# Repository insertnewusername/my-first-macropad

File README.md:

# my-first-macropad

My-first-macropad is.... My first macropad.
Made this to experiment with hardware, as I thought this would be a nice first project for me. Still decide what the buttons should do, they'll probably like execute simple commands such as opening task manager, I'll figure it out once I get the hardware and update this.

<H1>HARDWARE!!!</H1>
Ok so this was my first time soldering and assembling a pcb, so I screwed up a lot, and it took me a while to figure everything out (still need practice), and after I finished doing everything, getting the firmware done was a nightmare, so asked AI how do i make QMK not gimme that many error messages and what's wrong, eventually got there. Case is still pending, but the overall thing is done, so I don't think a case is that strictly required

IMAGES!!!!

(BTW I messed up the pcb which is why the usb for xiao is faced that way oopsies)

<h1>CAD Model: </h1><br>
Made a basic frame for all the keys and usb. Hopefully everthing works out!

<h1>PCD:</h1>

Here's my PCB, I made this all in KiCad.

<h1>BOM</h1>

Here's what I need to create the hackpad:

6x Cherry MX Switches <br>
6x DSA Keycaps <br>
4x M3x5x4 Heatset inserts <br>
4x M3x12mm SHSC Bolts <br>
6x 1N4148 DO-35 Diodes <br>
1x XIAO RP2040 <br>
1x Case (2 3D printed parts to assemble case I hope I get a 3d printer sometime next year) <br>
1x Soldering Iron (I'm new to hardware - this is my first project)<br>
<br>
(Optional - I'll try add these later but pls give cuz i'll find a way to add em)<br>
2x WS2812B LEDs<br>
1x 0.91" 128x32 OLED Display<br>

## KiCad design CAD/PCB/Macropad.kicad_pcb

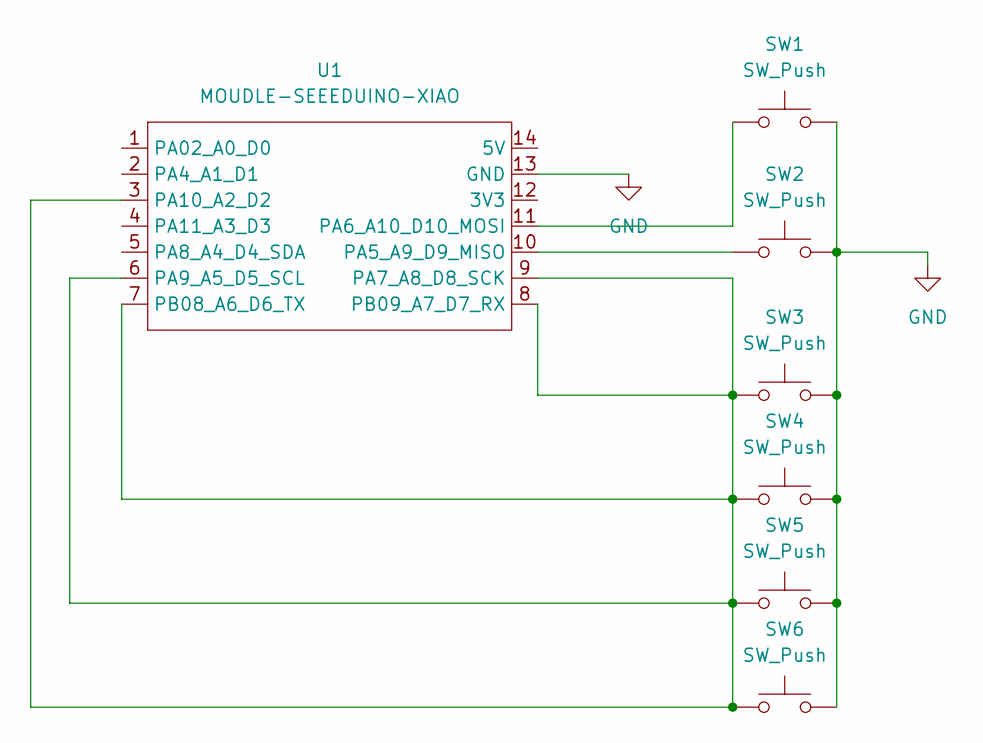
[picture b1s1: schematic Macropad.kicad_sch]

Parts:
SW1, SW2, SW3, SW4, SW5, SW6: SW_Push; SW_Cherry_MX_1.00u_PCB
U1: MOUDLE-SEEEDUINO-XIAO; XIAO-Generic-Hybrid-14P-2.54-21X17.8MM

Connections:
GND: SW1.2, SW2.2, SW3.2, SW4.2, SW5.2, SW6.2, U1.13 (GND)
unnamed: SW2.1, U1.10 (PA5_A9_D9_MISO)
unnamed: SW1.1, U1.11 (PA6_A10_D10_MOSI)
unnamed: SW3.1, SW4.1, SW5.1, SW6.1, U1.3 (PA10_A2_D2), U1.6 (PA9_A5_D5_SCL), U1.7 (PB08_A6_D6_TX), U1.8 (PB09_A7_D7_RX), U1.9 (PA7_A8_D8_SCK)

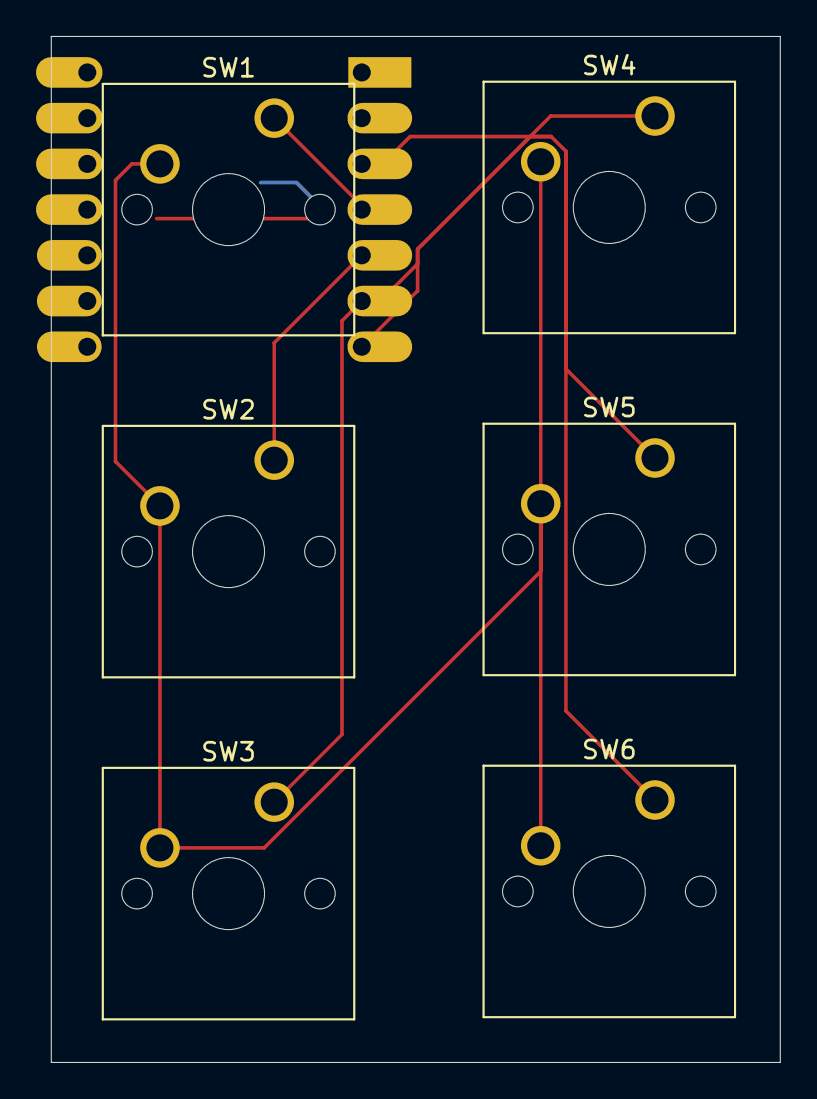
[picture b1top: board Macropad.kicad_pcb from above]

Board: 2 copper layers, 40.5 x 57.0 mm, 7 parts (1 on the bottom side), 4 nets.
